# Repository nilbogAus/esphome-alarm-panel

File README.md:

# esphome-alarm-panel

Prusa Printables 3D Model https://www.printables.com/model/973998-esphome-keypad-touchscreen <p>
PCBWAY PCB https://www.pcbway.com/project/shareproject/ESPHome_Keypad_touchscreen_21d7a82a.html

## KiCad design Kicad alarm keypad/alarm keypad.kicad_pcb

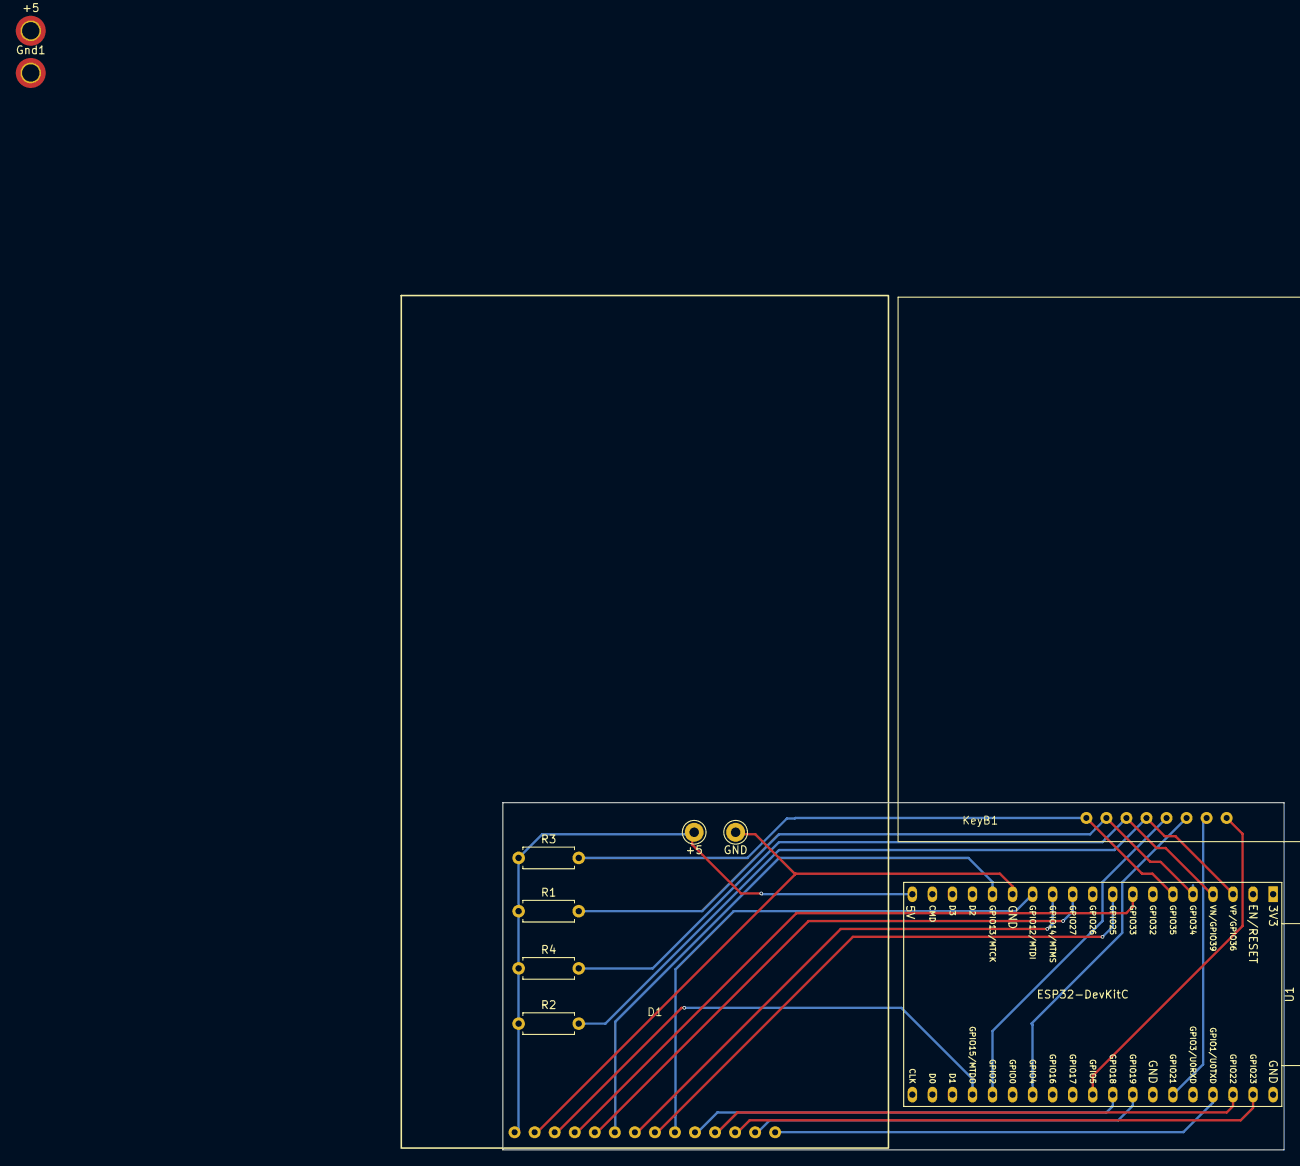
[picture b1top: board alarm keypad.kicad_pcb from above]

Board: 2 copper layers, 99.0 x 44.0 mm, 11 parts (0 on the bottom side), 22 nets.

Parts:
+5: MountingHole_Pad_MP; MountingHole_2.2mm_M2_DIN965_Pad_TopBottom
+5#2: Pin_D1.0mm_L10.0mm_LooseFit
D1: MSP4021
GND: Pin_D1.0mm_L10.0mm_LooseFit
Gnd1: MountingHole_2.2mm_M2_DIN965_Pad_TopBottom
KeyB1: Matrix Keypad 4x4
R1, R2, R3, R4: 100K; R_Axial_DIN0207_L6.3mm_D2.5mm_P7.62mm_Horizontal
U1: ESP32-DevKitC

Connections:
+5V: +5#2.1, D1.1 (VCC), R1.1, R2.1, R3.1, R4.1, U1.19 (5V)
GND: D1.2 (GND), GND.1, U1.14 (GND), U1.32 (GND), U1.38 (GND)
unnamed: D1.8 (LED), U1.9 (DAC_1/ADC2_CH8/GPIO25)
unnamed: D1.3 (TFT_CS), U1.23 (MTDO/GPIO15/ADC2_CH3)
unnamed: D1.4 (TFT_RESET), U1.8 (32K_XN/GPIO33/ADC1_CH5)
unnamed: D1.5 (TFT_RS(DC/RS)), U1.11 (ADC2_CH7/GPIO27)
unnamed: D1.7 (TFT_SCK), U1.12 (MTMS/GPIO14/ADC2_CH6)
unnamed: D1.6 (TFT_SDI(MOSI)), U1.15 (MTCK/GPIO13/ADC2_CH4)
unnamed: D1.9 (TFT_SDO(MISO)), U1.13 (MTDI/GPIO12/ADC2_CH5)
unnamed: D1.10 (TP_CLK), U1.30 (GPIO18)
unnamed: D1.11 (TP_CS), U1.36 (GPIO22)
unnamed: D1.12 (TP_DIN), U1.37 (GPIO23)
unnamed: D1.14 (TP_IRQ), U1.35 (U0TXD/GPIO1)
unnamed: D1.13 (TP_OUT(DO)), U1.31 (GPIO19)
unnamed: KeyB1.5 (C1), U1.24 (ADC2_CH2/GPIO2)
unnamed: KeyB1.6 (C2), U1.26 (ADC2_CH0/GPIO4)
unnamed: KeyB1.7 (C3), U1.33 (GPIO21)
unnamed: KeyB1.8 (C4), U1.29 (GPIO5)
unnamed: KeyB1.1 (R1), R3.2, U1.6 (VDET_2/GPIO35/ADC1_CH7)
unnamed: KeyB1.2 (R2), R4.2, U1.5 (VDET_1/GPIO34/ADC1_CH6)
unnamed: KeyB1.3 (R3), R1.2, U1.4 (SENSOR_VN/GPIO39/ADC1_CH3)
unnamed: KeyB1.4 (R4), R2.2, U1.3 (SENSOR_VP/GPIO36/ADC1_CH0)

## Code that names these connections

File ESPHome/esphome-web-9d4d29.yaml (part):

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output:
  - id: backlight_output
    platform: gpio
    pin: GPIO25

light:
  - platform: binary
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#ST7796 display
spi:
  - id: display_spi
    clk_pin: GPIO14
    mosi_pin: GPIO13
    miso_pin: 
      number: GPIO12
      ignore_strapping_warning: true 
  - id: touch_spi
    clk_pin: GPIO18
    mosi_pin: GPIO23
    miso_pin: GPIO19 

display:
  - platform: ili9xxx
    model: ST7796
    id: my_display
    spi_id: display_spi
    dc_pin: GPIO27
    reset_pin: GPIO33
    cs_pin: 
      number: GPIO15
      ignore_strapping_warning: true 
    dimensions:  #320x480 only possible with psram
      width: 320
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    y_max: 3960 
  id: my_touchscreen
  spi_id: touch_spi
  cs_pin: GPIO22
  interrupt_pin: GPIO01
  on_touch:
    - lambda: |-
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
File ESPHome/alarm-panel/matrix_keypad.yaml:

matrix_keypad:
  id: keypad
  columns:
    - pin: 
        number: GPIO35
        mode: 
          input: True
    - pin: 
        number: GPIO34
        mode: 
          input: True
    - pin: 
        number: GPIO39
        mode: 
          input: True
    - pin: 
        number: GPIO36
        mode: 
          input: True  
  rows:
    - pin: 
        number: GPIO02
        mode: 
          output: True  
        ignore_strapping_warning: true  
    - pin:  
        number: GPIO04
        mode: 
          output: True 
    - pin:  
        number: GPIO21
        mode: 
          output: True     
    - pin:  
        number: GPIO05
        mode: 
          output: True  
        ignore_strapping_warning: true             
  keys: "123A456B789C*0#D"
  has_diodes: false  
  
          
    

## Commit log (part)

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2025-08-21 fix merge
2025-08-21 code cleanup
2025-08-21 add help page
2025-08-24 fix uptime
2025-08-26 add dehumidifier button
2025-08-26 fix touchscreen buttons
2025-09-02 sign error
2025-09-03 fix help typo
2025-09-07 fix blind buttone
2025-09-07 fix blind buttons
2025-09-11 fix pool swith
2025-09-11 stairs sign button
2025-09-11 reduce glyphs
2025-09-12 blind buttons
2025-11-10 test ILI9488
2026-04-22 fix blank
2026-05-14 test different screen
2026-05-14 Change display model from ili9488 to ST7735
2026-05-15 Add CS pin configuration for display with warning suppression
2026-05-15 multi displays
2026-05-17 fix: correct glyphs in roboto_lrg font definition
2026-05-17 feat: update button text and add new icon for screen control
2026-05-19 feat: replace dehumidifier switch with backlight control and update keypad button state
2026-05-19 feat: remove dehumidifier switch and add backlight control with delay
2026-05-19 feat: update backlight delay from 10s to 8h
2026-05-19 feat: change backlight output platform from gpio to ledc and update light platform to monochromatic
2026-05-19 feat: remove backlight output level adjustment on turn off
2026-05-19 fix: adjust text alignment for keypad button 1
2026-05-19 fix: adjust text formatting for keypad button labels
2026-05-19 fix: update text formatting for keypad button labels
2026-06-19 feat: update outside temperature sensor entity_id and add advanced sram1_as_iram option
